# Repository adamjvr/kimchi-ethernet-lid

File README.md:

# kimchi-ethernet-lid
A simple lid for the GroupGets Kimchi Miro SBC that adds gigabit Ethernet in a compact package

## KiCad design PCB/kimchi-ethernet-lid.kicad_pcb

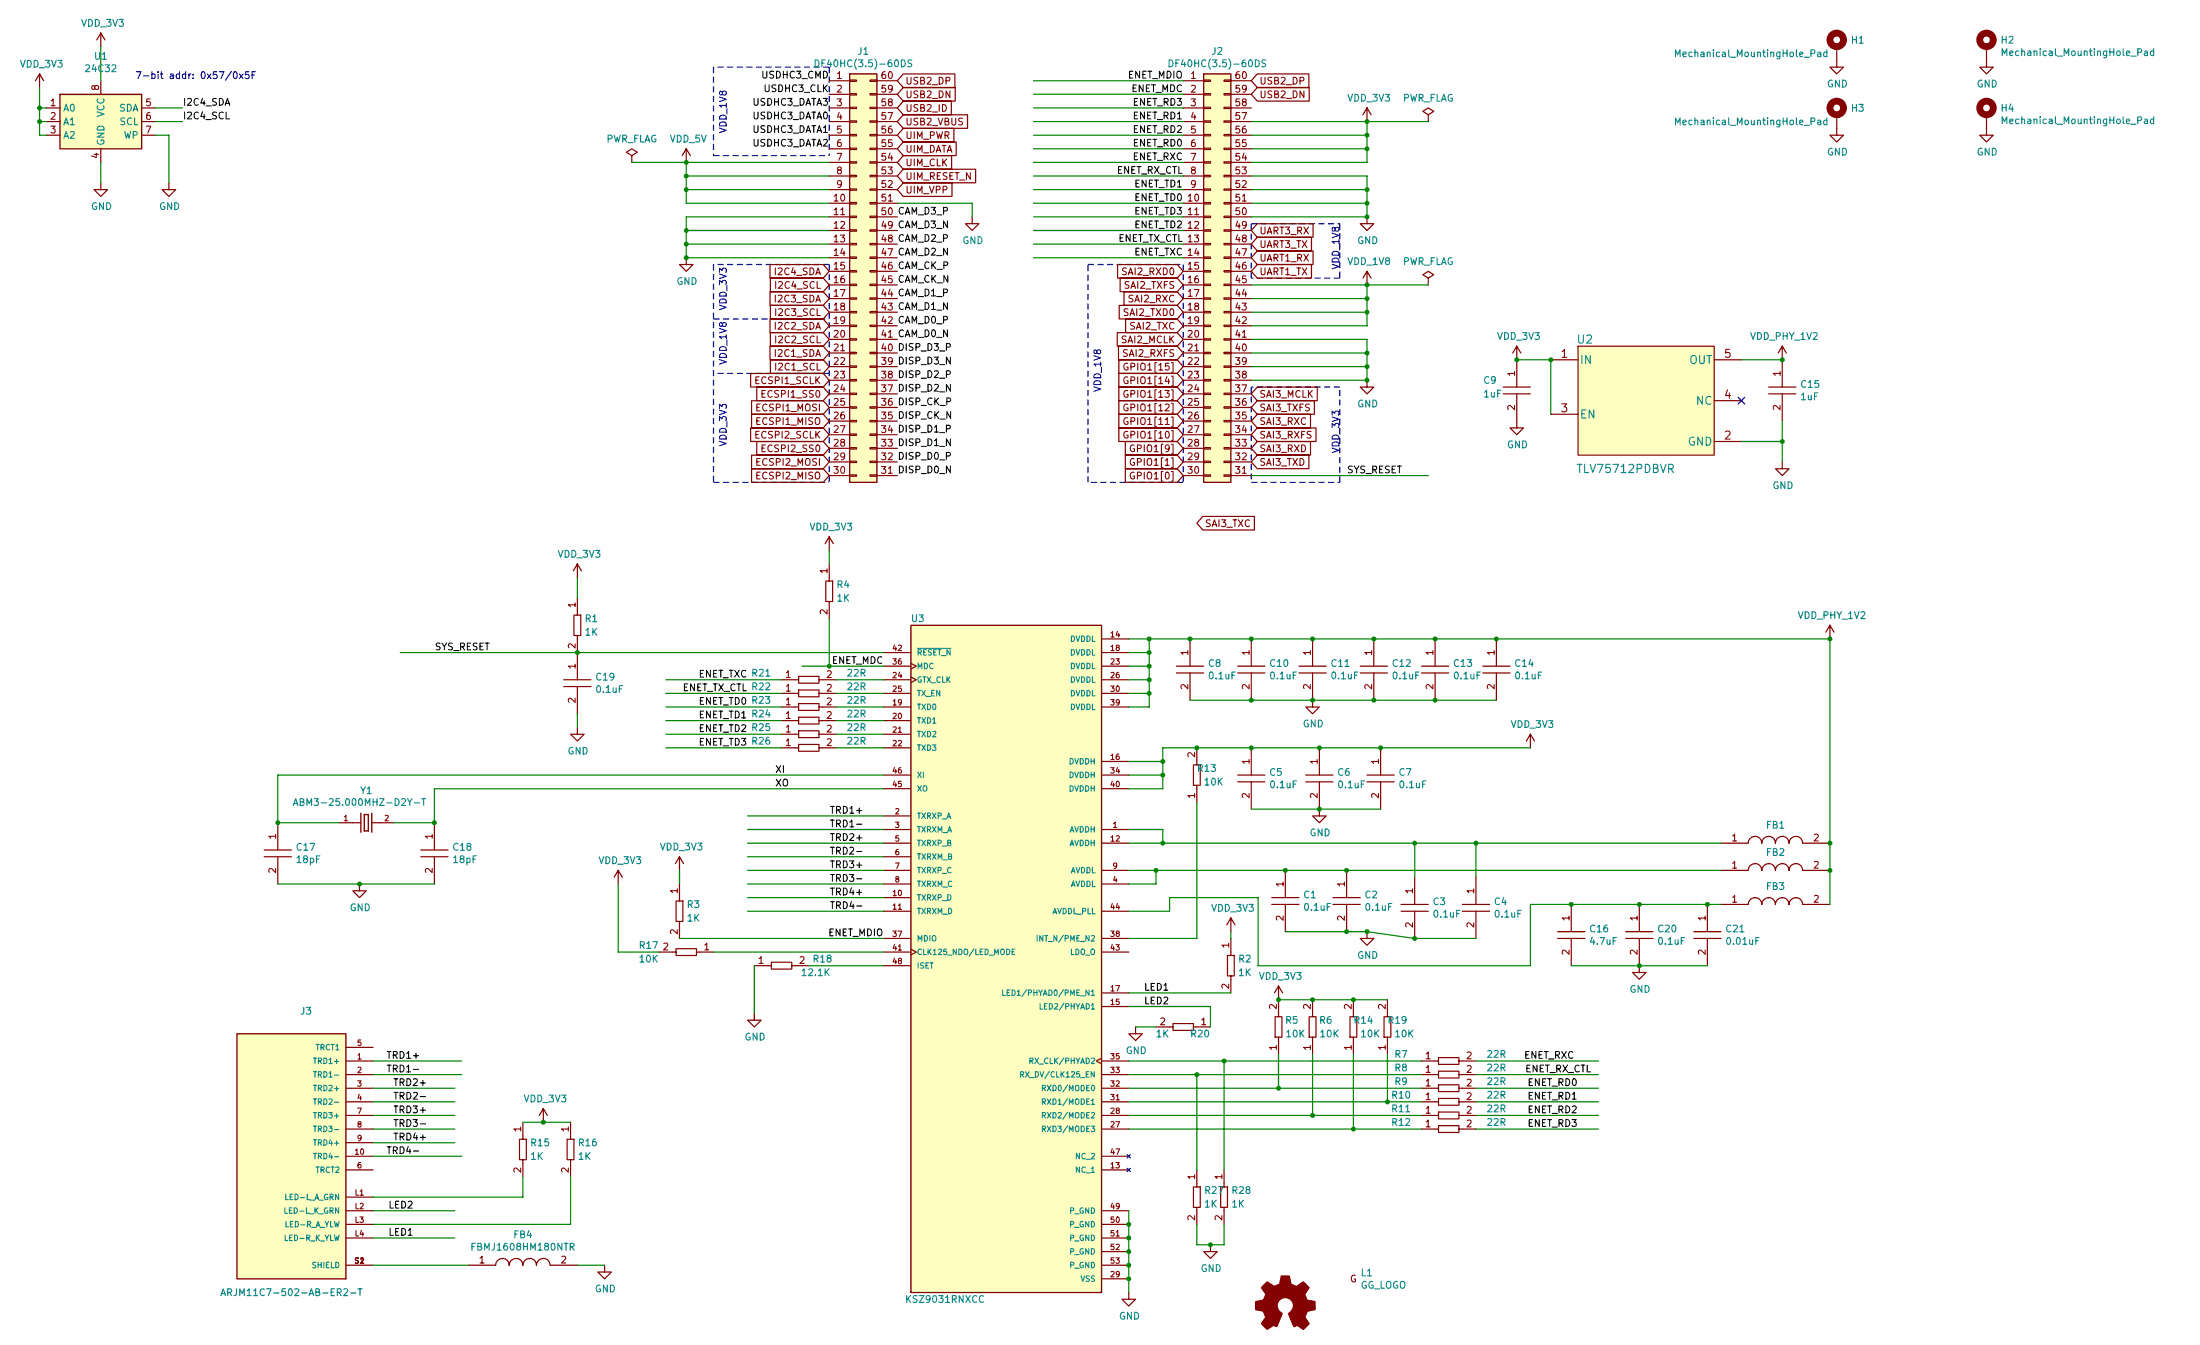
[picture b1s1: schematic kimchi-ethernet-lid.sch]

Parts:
C1, C2, C3, C4, C5, C6, C7, C8, C10, C11, C12, C13, C14, C19, C20: C0402C104K9PACTU; R0402; Tolerance 10%; Voltage 6.3V; MFR# C0402C104K9PACTU
C9, C15: 0402ZD105KAT2A; R0402; Tolerance 10%; Voltage 10V; MFR# 0402ZD105KAT2A
C16: GRM155R61A475MEAAD; C0402; Tolerance 20%; Voltage 10V; MFR# GRM155R61A475MEAAD
C17, C18: 04025A180GAT2A; C0402; Tolerance 2%; Voltage 50V; MFR# 04025A180GAT2A
C21: C0603C103KARACAUTO; C0603; Tolerance 10%; Voltage 250V; MFR# C0603C103KARACAUTO
FB1, FB2, FB3: MMZ1005S601CTD25; R0402; Tolerance *; Voltage *; MFR# MMZ1005S601CTD25
FB4: FBMJ1608HM180NTR; R0603; Tolerance *; Voltage *; MFR# FBMJ1608HM180NTR
H1, H2, H3, H4: Mechanical_MountingHole_Pad; MountingHole_3mm_Pad
J1, J2: DF40HC(3.5)-60DS
J3: ARJM11C7-502-AB-ER2-T; ABRACON_ARJM11C7-502-AB-ER2-T; PARTREV 04.22.2019
L1: GG_LOGO; groupgets_logo
LOGO1: Graphic_Logo_Open_Hardware_Small; OSHW-Logo_5.7x6mm_SilkScreen
R1, R2, R3, R4, R15, R16, R20, R27, R28: RC0402FR-071KL; R0402; Tolerance 1%; Voltage *; MFR# RC0402FR-071KL
R5, R6, R13, R14, R17, R19: RC0402FR-0710KL; R0402; Tolerance 1%; Voltage *; MFR# RC0402FR-0710KL
R7, R8, R9, R10, R11, R12, R21, R22, R23, R24, R25, R26: RC0402FR-0722RL; R0402; Tolerance 1%; Voltage *; MFR# RC0402FR-0722RL
R18: RMCF0402FT12K1; R0402; Tolerance 1%; Voltage *; MFR# RMCF0402FT12K1
U1: 24C32; DFN-8-1EP_3x2mm_P0.5mm_EP1.36x1.46mm; Part M24C32-FMC6TG
U2: TLV75712PDBVR
U3: KSZ9031RNXCC; QFN50P700X700X90-49N
Y1: ABM3-25.000MHZ-D2Y-T; XTAL500X320X130N

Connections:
/CAM_CK_N: J1.45
/CAM_CK_P: J1.46
/CAM_D0_N: J1.41
/CAM_D0_P: J1.42
/CAM_D1_N: J1.43
/CAM_D1_P: J1.44
/CAM_D2_N: J1.47
/CAM_D2_P: J1.48
/CAM_D3_N: J1.49
/CAM_D3_P: J1.50
/DISP_CK_N: J1.35
/DISP_CK_P: J1.36
/DISP_D0_N: J1.31
/DISP_D0_P: J1.32
/DISP_D1_N: J1.33
/DISP_D1_P: J1.34
/DISP_D2_N: J1.37
/DISP_D2_P: J1.38
/DISP_D3_N: J1.39
/DISP_D3_P: J1.40
/ENET_MDC: J2.2, R4.2, U3.36 (MDC)
/ENET_MDIO: J2.1, R3.2, U3.37 (MDIO); also elsewhere on the board
/ENET_RD0: J2.6, R9.2
/ENET_RD1: J2.4, R10.2
/ENET_RD2: J2.5, R11.2
/ENET_RD3: J2.3, R12.2
/ENET_RXC: J2.7, R7.2
/ENET_RX_CTL: J2.8, R8.2
/ENET_TD0: J2.10, R23.1
/ENET_TD1: J2.9, R24.1
/ENET_TD2: J2.12, R25.1
/ENET_TD3: J2.11, R26.1
/ENET_TXC: J2.14, R21.1
/ENET_TX_CTL: J2.13, R22.1
/LED1: J3.L4 (LED-R_K_YLW), R2.2, U3.17 (LED1/PHYAD0/PME_N1)
/LED2: J3.L2 (LED-L_K_GRN), R20.1, U3.15 (LED2/PHYAD1)
/SYS_RESET: C19.1, J2.31, R1.2, U3.42 (~RESET_N)
/TRD1+: J3.1 (TRD1+), U3.2 (TXRXP_A)
/TRD1-: J3.2 (TRD1-), U3.3 (TXRXM_A)
/TRD2+: J3.3 (TRD2+), U3.5 (TXRXP_B)
/TRD2-: J3.4 (TRD2-), U3.6 (TXRXM_B)
/TRD3+: J3.7 (TRD3+), U3.7 (TXRXP_C)
/TRD3-: J3.8 (TRD3-), U3.8 (TXRXM_C)
/TRD4+: J3.9 (TRD4+), U3.10 (TXRXP_D)
/TRD4-: J3.10 (TRD4-), U3.11 (TXRXM_D)
/USDHC3_CLK: J1.2
/USDHC3_CMD: J1.1
/USDHC3_DATA0: J1.4
/USDHC3_DATA1: J1.5
/USDHC3_DATA2: J1.6
/USDHC3_DATA3: J1.3
/XI: C17.1, U3.46 (XI), Y1.1
/XO: C18.1, U3.45 (XO), Y1.2
ECSPI1_MISO: J1.26
ECSPI1_MOSI: J1.25
ECSPI1_SCLK: J1.23
ECSPI1_SS0: J1.24
ECSPI2_MISO: J1.30
ECSPI2_MOSI: J1.29
ECSPI2_SCLK: J1.27
ECSPI2_SS0: J1.28
GND: C1.2, C2.2, C3.2, C4.2, C5.2, C6.2, C7.2, C8.2, C9.2, C10.2, C11.2, C12.2, C13.2, C14.2, C15.2, C16.2, C17.2, C18.2, C19.2, C20.2, C21.2, FB4.2, H1.1, H2.1, H3.1, H4.1, J1.11, J1.12, J1.13, J1.14, J1.51, J2.38, J2.39, J2.40, J2.41, J2.50, J2.51, J2.52, J2.53, R18.1, R20.2, R27.2, R28.2, U1.4 (GND), U1.7 (WP), U2.2 (GND), U3.29 (VSS), U3.49 (P_GND), U3.50 (P_GND), U3.51 (P_GND), U3.52 (P_GND), U3.53 (P_GND)
GPIO1[0]: J2.30
GPIO1[1]: J2.29
GPIO1[9]: J2.28
GPIO1[10]: J2.27
GPIO1[11]: J2.26
GPIO1[12]: J2.25
GPIO1[13]: J2.24
GPIO1[14]: J2.23
GPIO1[15]: J2.22
I2C1_SCL: J1.22
I2C1_SDA: J1.21
I2C2_SCL: J1.20
I2C2_SDA: J1.19
I2C3_SCL: J1.18
I2C3_SDA: J1.17
I2C4_SCL: J1.16, U1.6 (SCL)
I2C4_SDA: J1.15, U1.5 (SDA)
unnamed: C1.1, C2.1, FB2.1, U3.4 (AVDDL), U3.9 (AVDDL)
unnamed: C3.1, C4.1, FB1.1, U3.1 (AVDDH), U3.12 (AVDDH)
unnamed: C16.1, C20.1, C21.1, FB3.1, U3.44 (AVDDL_PLL)
unnamed: FB4.1, J3.S1 (SHIELD), J3.S2 (SHIELD)
unnamed: J3.L1 (LED-L_A_GRN), R15.2
unnamed: J3.L3 (LED-R_A_YLW), R16.2
unnamed: R5.1, R9.1, U3.32 (RXD0/MODE0)
unnamed: R10.1, R19.1, U3.31 (RXD1/MODE1)
unnamed: R6.1, R11.1, U3.28 (RXD2/MODE2)
unnamed: R12.1, R14.1, U3.27 (RXD3/MODE3)
unnamed: R13.1, U3.38 (INT_N/PME_N2)
unnamed: R17.1, U3.41 (CLK125_NDO/LED_MODE)
unnamed: R18.2, U3.48 (ISET)
unnamed: R21.2, U3.24 (GTX_CLK)
unnamed: R22.2, U3.25 (TX_EN)
unnamed: R23.2, U3.19 (TXD0)
unnamed: R24.2, U3.20 (TXD1)
unnamed: R25.2, U3.21 (TXD2)
unnamed: R26.2, U3.22 (TXD3)
unnamed: R8.1, R27.1, U3.33 (RX_DV/CLK125_EN)
unnamed: R7.1, R28.1, U3.35 (RX_CLK/PHYAD2)
SAI2_MCLK: J2.20
SAI2_RXC: J2.17
SAI2_RXD0: J2.15
SAI2_RXFS: J2.21
SAI2_TXC: J2.19
SAI2_TXD0: J2.18
SAI2_TXFS: J2.16
SAI3_MCLK: J2.37
SAI3_RXC: J2.35
SAI3_RXD: J2.33
SAI3_RXFS: J2.34
SAI3_TXD: J2.32
SAI3_TXFS: J2.36
UART1_RX: J2.47
UART1_TX: J2.46
UART3_RX: J2.49
UART3_TX: J2.48
UIM_CLK: J1.54
UIM_DATA: J1.55
UIM_PWR: J1.56
UIM_RESET_N: J1.53
UIM_VPP: J1.52
USB2_DN: J1.59, J2.59
USB2_DP: J1.60, J2.60
USB2_ID: J1.58
USB2_VBUS: J1.57
VDD_1V8: J2.42, J2.43, J2.44, J2.45
VDD_3V3: C5.1, C6.1, C7.1, C9.1, J2.54, J2.55, J2.56, J2.57, R1.1, R2.1, R3.1, R4.1, R5.2, R6.2, R13.2, R14.2, R15.1, R16.1, R17.2, R19.2, U1.1 (A0), U1.2 (A1), U1.3 (A2), U1.8 (VCC), U2.1 (IN), U2.3 (EN), U3.16 (DVDDH), U3.34 (DVDDH), U3.40 (DVDDH); also elsewhere on the board
VDD_5V: J1.7, J1.8, J1.9, J1.10
VDD_PHY_1V2: C8.1, C10.1, C11.1, C12.1, C13.1, C14.1, C15.1, FB1.2, FB2.2, FB3.2, U2.5 (OUT), U3.14 (DVDDL), U3.18 (DVDDL), U3.23 (DVDDL), U3.26 (DVDDL), U3.30 (DVDDL), U3.39 (DVDDL)

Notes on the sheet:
7-bit addr: 0x57/0x5F
VDD_1V8
VDD_3V3

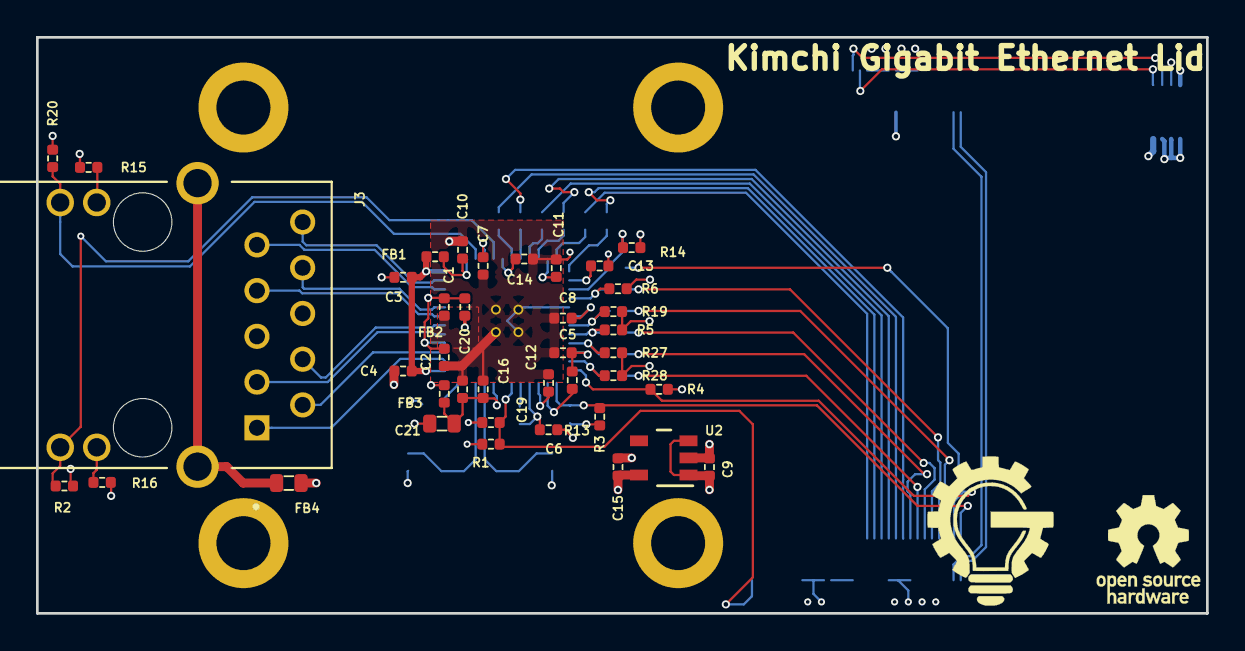
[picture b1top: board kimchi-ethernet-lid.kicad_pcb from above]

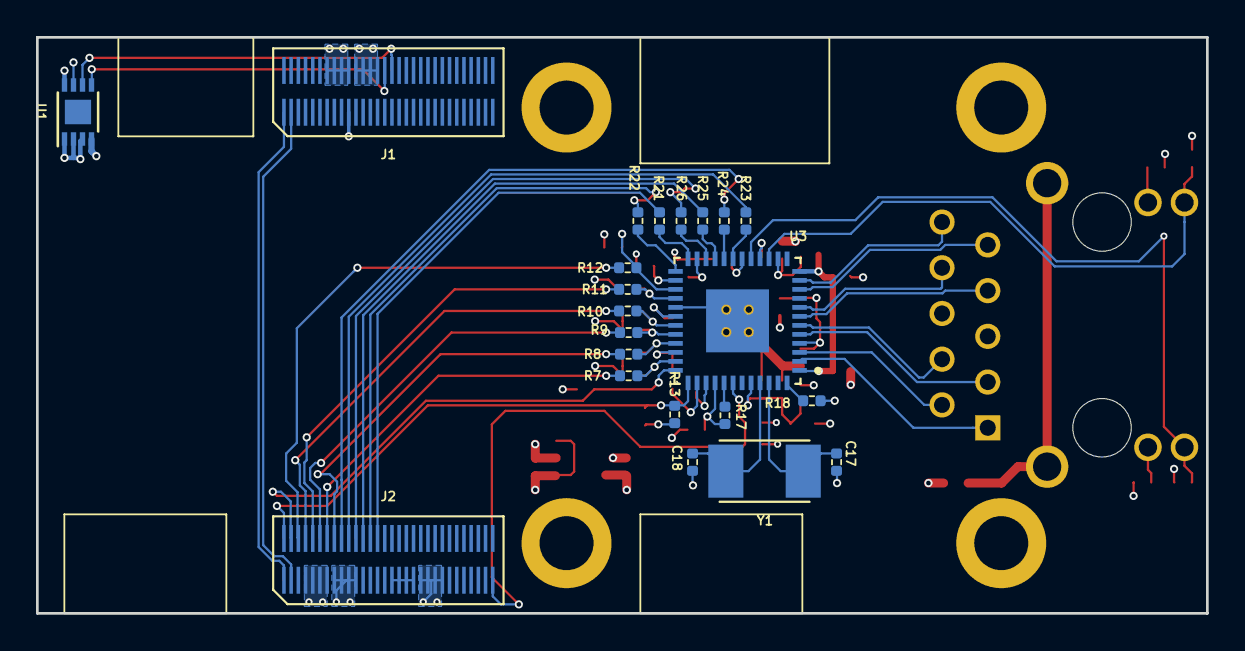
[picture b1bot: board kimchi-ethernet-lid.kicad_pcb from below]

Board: 4 copper layers, 65.0 x 32.0 mm, 67 parts (22 on the bottom side), 57 nets.

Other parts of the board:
R13#2: RC0402FR-074K7L; R0402

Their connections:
/ENET_MDIO: R13#2.2; also elsewhere on the board
VDD_3V3: R13#2.1; also elsewhere on the board

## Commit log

2021-04-27 Template Project Import
    Imported Template project form the GroupGets repository for Kimchi lid templates. Changed file names over to create project for ethernet-lid. work in progress.
2021-04-30 Libraries, Schematic Capture, Part Placement, Lauout
    Created and added all realted components. Completed schematic capture. Part placement all bu down, layout in progress since schematic capture.
    Had to change out mag jacks a lot to find one that would fit the design
2021-04-30 Change in design
    Swapped orientation of PHY and position of ethernet connector, moving computers
2021-04-30 small schematic tweak that didn't get synced
    d
2021-05-03 Route Complete
    RMGII signals routed to kimchi headers, ENET diff pairs tuned routed to connector. Power distribution scheme designed and implemented. First pass of route done, Further analysis need for RGMII interf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
2021-05-04 Memory Module
    Memory module moved, USB to PCIe passthrough added. BOM created in libreoffice format, CSV from component fields also generated.
2021-06-02 Pullups
    Pullup resistors added to RGMII interface setup on boot.
2021-06-03 Silkscreen Tweak and BOM
    Tweaked silkscreen text size and created order BOM
2021-06-15 DRC and Sys_Reset
    Fixed some small DRC violations. zeroed out soldermask settings so that fab can decide their own. Tied SYS_RESET signal to muxable GPIO pin on Kimchi header.
